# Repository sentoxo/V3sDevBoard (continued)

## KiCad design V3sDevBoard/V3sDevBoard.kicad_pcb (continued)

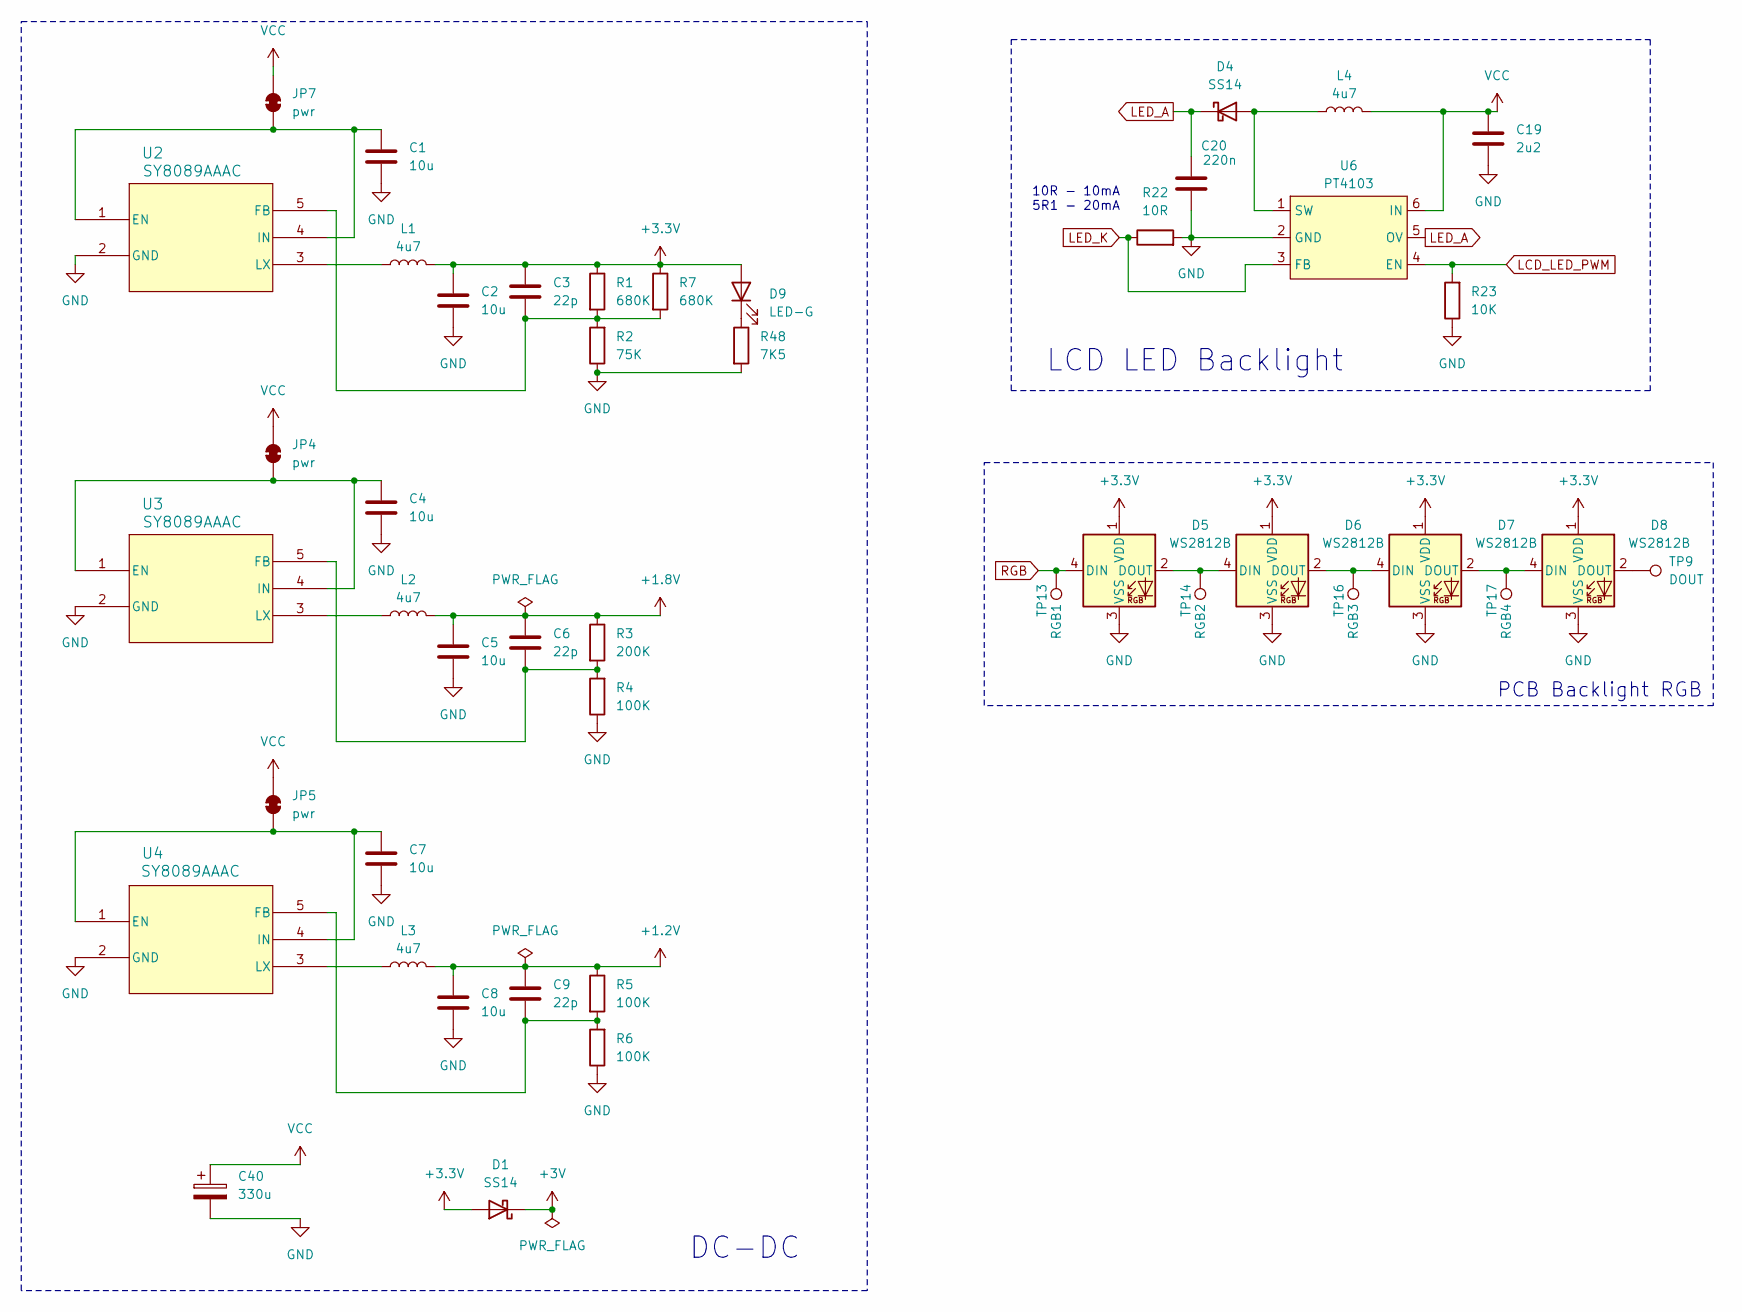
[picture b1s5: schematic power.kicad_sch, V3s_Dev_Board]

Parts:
C1, C2, C4, C5, C7, C8: 10u; C_1206_3216Metric
C3, C6, C9: 22p; C_0805_2012Metric_Pad1.18x1.45mm_HandSolder
C19: 2u2; C_0805_2012Metric_Pad1.18x1.45mm_HandSolder
C20: 220n; C_0805_2012Metric_Pad1.18x1.45mm_HandSolder
C40: 330u; CP_EIA-7343-15_Kemet-W_HandSolder
D1, D4: SS14; D_SMA
D5, D6, D7, D8: WS2812B; LED_WS2812B_PLCC4_5.0x5.0mm_P3.2mm
D9: LED-G; LED_0805_2012Metric_Pad1.15x1.40mm_HandSolder
JP4, JP5, JP7: pwr; SolderJumper-2_P1.3mm_Bridged_RoundedPad1.0x1.5mm
L1, L2, L3, L4: 4u7; L_APV_APH0420_HandSolder
R1: 680K; R_0603_1608Metric_Pad0.98x0.95mm_HandSolder
R2: 75K; R_0603_1608Metric_Pad0.98x0.95mm_HandSolder
R3: 200K; R_0603_1608Metric_Pad0.98x0.95mm_HandSolder
R4, R5, R6: 100K; R_0603_1608Metric_Pad0.98x0.95mm_HandSolder
R7: 680K; R_0805_2012Metric_Pad1.20x1.40mm_HandSolder
R22: 10R; R_0805_2012Metric_Pad1.20x1.40mm_HandSolder
R23: 10K; R_0603_1608Metric_Pad0.98x0.95mm_HandSolder
R48: 7K5; R_0603_1608Metric_Pad0.98x0.95mm_HandSolder
TP9: DOUT; TestPoint_Pad_D1.0mm
TP13: RGB1; TestPoint_Pad_D1.0mm
TP14: RGB2; TestPoint_Pad_D1.0mm
TP16: RGB3; TestPoint_Pad_D1.0mm
TP17: RGB4; TestPoint_Pad_D1.0mm
U2, U3, U4: SY8089AAAC; SY8089AAAC_SGY
U6: PT4103; SOT-23-6_Handsoldering

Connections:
+1.2V: C8.1, C9.1, L3.2, R5.1; also elsewhere on the board
+1.8V: C5.1, C6.1, L2.2, R3.1; also elsewhere on the board
+3.3V: C2.1, C3.1, D1.2 (A), D5.1 (VDD), D6.1 (VDD), D7.1 (VDD), D8.1 (VDD), D9.2 (A), L1.2, R1.1, R7.1; also elsewhere on the board
+3V: D1.1 (K); also elsewhere on the board
GND: C1.2, C2.2, C4.2, C5.2, C7.2, C8.2, C19.2, C20.2, C40.2, D5.3 (VSS), D6.3 (VSS), D7.3 (VSS), D8.3 (VSS), R2.1, R4.1, R6.1, R22.2, R23.1, R48.2, U2.2 (GND), U3.2 (GND), U4.2 (GND), U6.2 (GND); also elsewhere on the board
LCD_LED_PWM: R23.2, U6.4 (EN); also elsewhere on the board
LED_A: C20.1, D4.1 (K), U6.5 (OV); also elsewhere on the board
LED_K: R22.1, U6.3 (FB); also elsewhere on the board
unnamed: D4.2 (A), L4.1, U6.1 (SW)
unnamed: D5.2 (DOUT), D6.4 (DIN), TP14.1 (1_1)
unnamed: D6.2 (DOUT), D7.4 (DIN), TP16.1 (1_1)
unnamed: D7.2 (DOUT), D8.4 (DIN), TP17.1 (1_1)
unnamed: D8.2 (DOUT), TP9.1 (1_1)
unnamed: D9.1 (K), R48.1
unnamed: C4.1, JP4.1 (A), U3.1 (EN), U3.4 (IN)
unnamed: C7.1, JP5.1 (A), U4.1 (EN), U4.4 (IN)
unnamed: C1.1, JP7.1 (A), U2.1 (EN), U2.4 (IN)
unnamed: C3.2, R1.2, R2.2, R7.2, U2.5 (FB)
unnamed: L1.1, U2.3 (LX)
unnamed: C6.2, R3.2, R4.2, U3.5 (FB)
unnamed: L2.1, U3.3 (LX)
unnamed: C9.2, R5.2, R6.2, U4.5 (FB)
unnamed: L3.1, U4.3 (LX)
RGB: D5.4 (DIN), TP13.1 (1_1); also elsewhere on the board
VCC: C19.1, C40.1, JP4.2 (B), JP5.2 (B), JP7.2 (B), L4.2, U6.6 (IN); also elsewhere on the board

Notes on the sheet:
10R - 10mA 5R1 - 20mA
LCD LED Backlight
PCB Backlight RGB
DC-DC

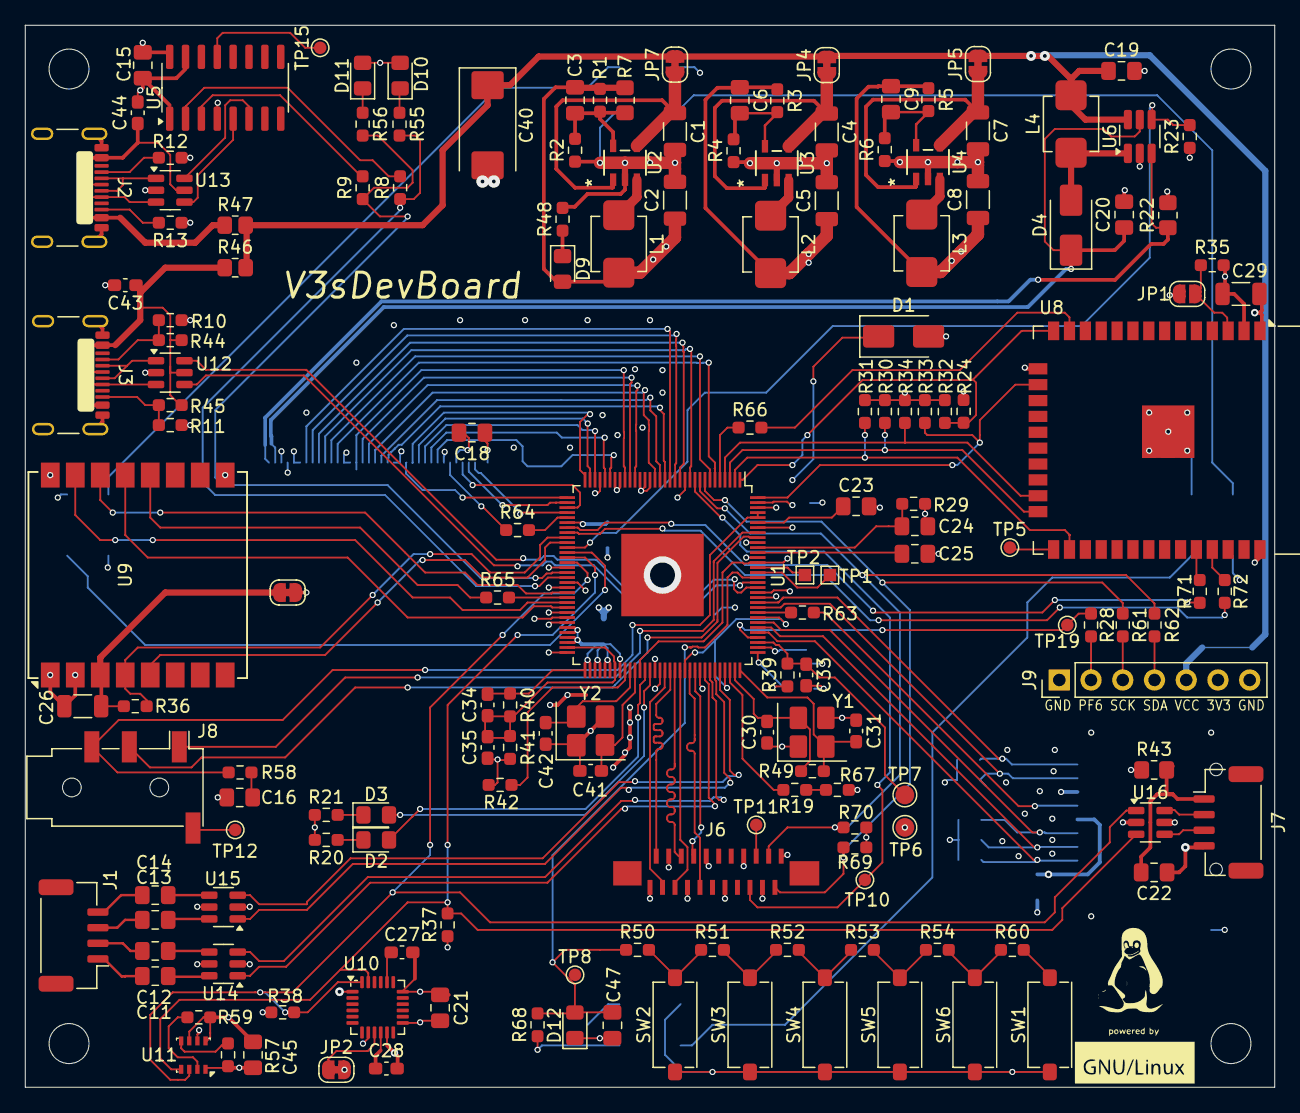
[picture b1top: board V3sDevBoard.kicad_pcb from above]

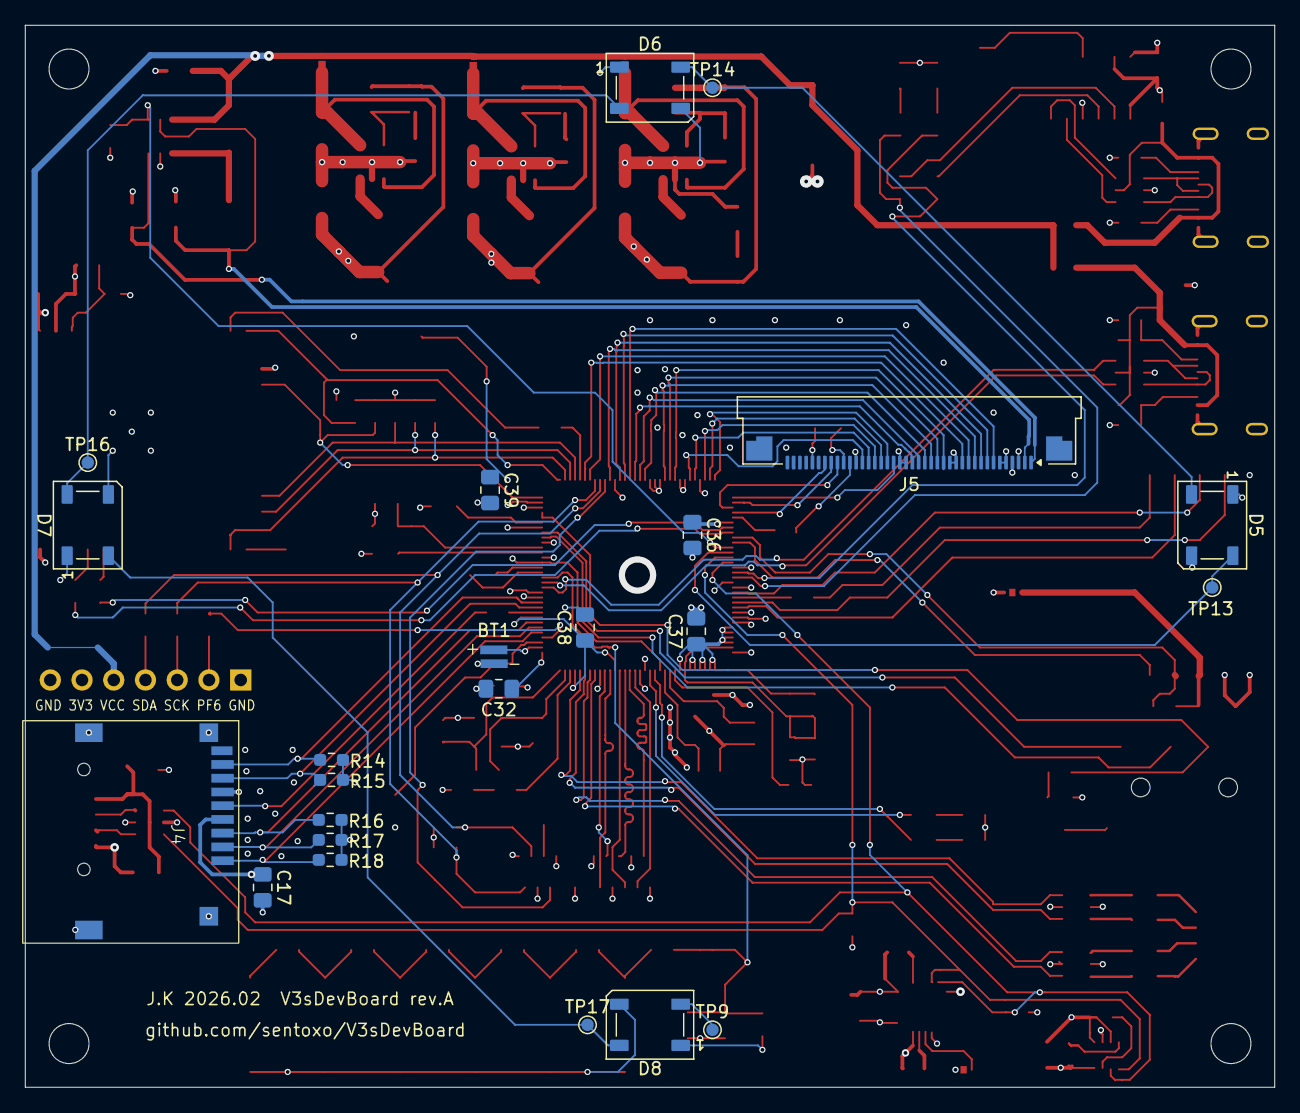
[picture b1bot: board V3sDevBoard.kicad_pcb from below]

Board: 4 copper layers, 100.0 x 85.0 mm, 189 parts (23 on the bottom side), 165 nets.

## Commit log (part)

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2025-12-23 Init
2025-12-24 drawing schematic
2025-12-25 drawing schematics
2025-12-26 advancing in schematics and footprints
    Making needed custom footprints for connectors, adding a lot of small changes to schematics.
2025-12-28 completing schematics
    completing schematics, adding netclasses, fixing bugs, updating readme, starting pcb
2025-12-30 first attempts to arrange components on a PCB
    plus making footprints bme280&mpu6050 easier to hand solder.
2026-02-05 completing pcb desgin
    Returning to project after month away. Switching to 4-layer desgin on 3313 stackup sig-gnd-pow-sig, changing size of some passive to 0603, connecting all components, adding silkscreen.
2026-02-16 last changes and sending to manufacturing
2026-05-02 fixing errors in revA
    Fixing:
    - Ther was mistake in SDIO for SDCard. Swaped data lines.
    - RTC didn't have power without battery.
    Updating readme.
2026-05-02 updating readme
